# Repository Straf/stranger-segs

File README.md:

STRANGER SEGS
=============

An hardware platform to play with 7-segment displays.

This project was submitted to the montly challenge of the Element14 community (April 2022).
This repository contains all the artifacts developed for the challenge.

What you need
-------------

* The schematics and the PCB were produced with [KiCad 5.1.12](https://www.kicad.org).

* The firmware of the two applications was developed with [Microchip MPLAB X IDE 6.00](https://www.microchip.com/en-us/tools-resources/develop/mplab-x-ide) and the [Microchip AVR-GCC 5.4.0](https://www.microchip.com/en-us/tools-resources/develop/microchip-studio/gcc-compilers).

    - The first application is a **minimalist** racing game which may be played with a key and a display.

    - The second application is the firmware of a smart display module. Each module may be chained to others or composed in arbitrary display trees.

* The application to feed the display chain with data can be compiled with any **GCC** toolchain for a POSIX system. The build system is `make`. Built and tested on **macOS**, with [VSCode](https://code.visualstudio.com) as the IDE. It may work with Linux and [Cygwin](https://www.cygwin.com) for Windows.

### To build the firmware

1. First open the project with MPLAB X (some `makefile`s must be regenerated by the IDE).

2. Choose the exact part which you wish to use. The firmware should work with any **tinyavr 0** or **tinyavr 1** with enough RAM and flash to run the application. The game requires ~3KB of flash. The smart module less than 2KB. The use of RAM is negligible. The hardware module requires a **20-Pin VQFN** package.

3. Install the Device Family Pack of the part you wish to use.

4. Finally, build the application.

### To program the firmware into a module

To be programmed, the hardware module requires a [6-pin Tag-Connect cable](https://www.tag-connect.com/product-category/products/cables/6-pin-target) and a compatible programming tool, such as the **Atmel-ICE** or the **PicKit4**.

Since the **tinyavr** used have a **UPDI** interface, you may also use a simple USB-to-serial adapter with [pymcuprog](https://github.com/microchip-pic-avr-tools/pymcuprog).

### To build the driver application

A simple `make` should suffice.

Other resources
---------------

The project is described in two blog posts in the E14 community.

* The [first post](https://community.element14.com/challenges-projects/project14/7segmentdisplay/b/blog/posts/stranger-segs);

* The [second post](https://community.element14.com/challenges-projects/project14/7segmentdisplay/b/blog/posts/stranger-segs---season-two).

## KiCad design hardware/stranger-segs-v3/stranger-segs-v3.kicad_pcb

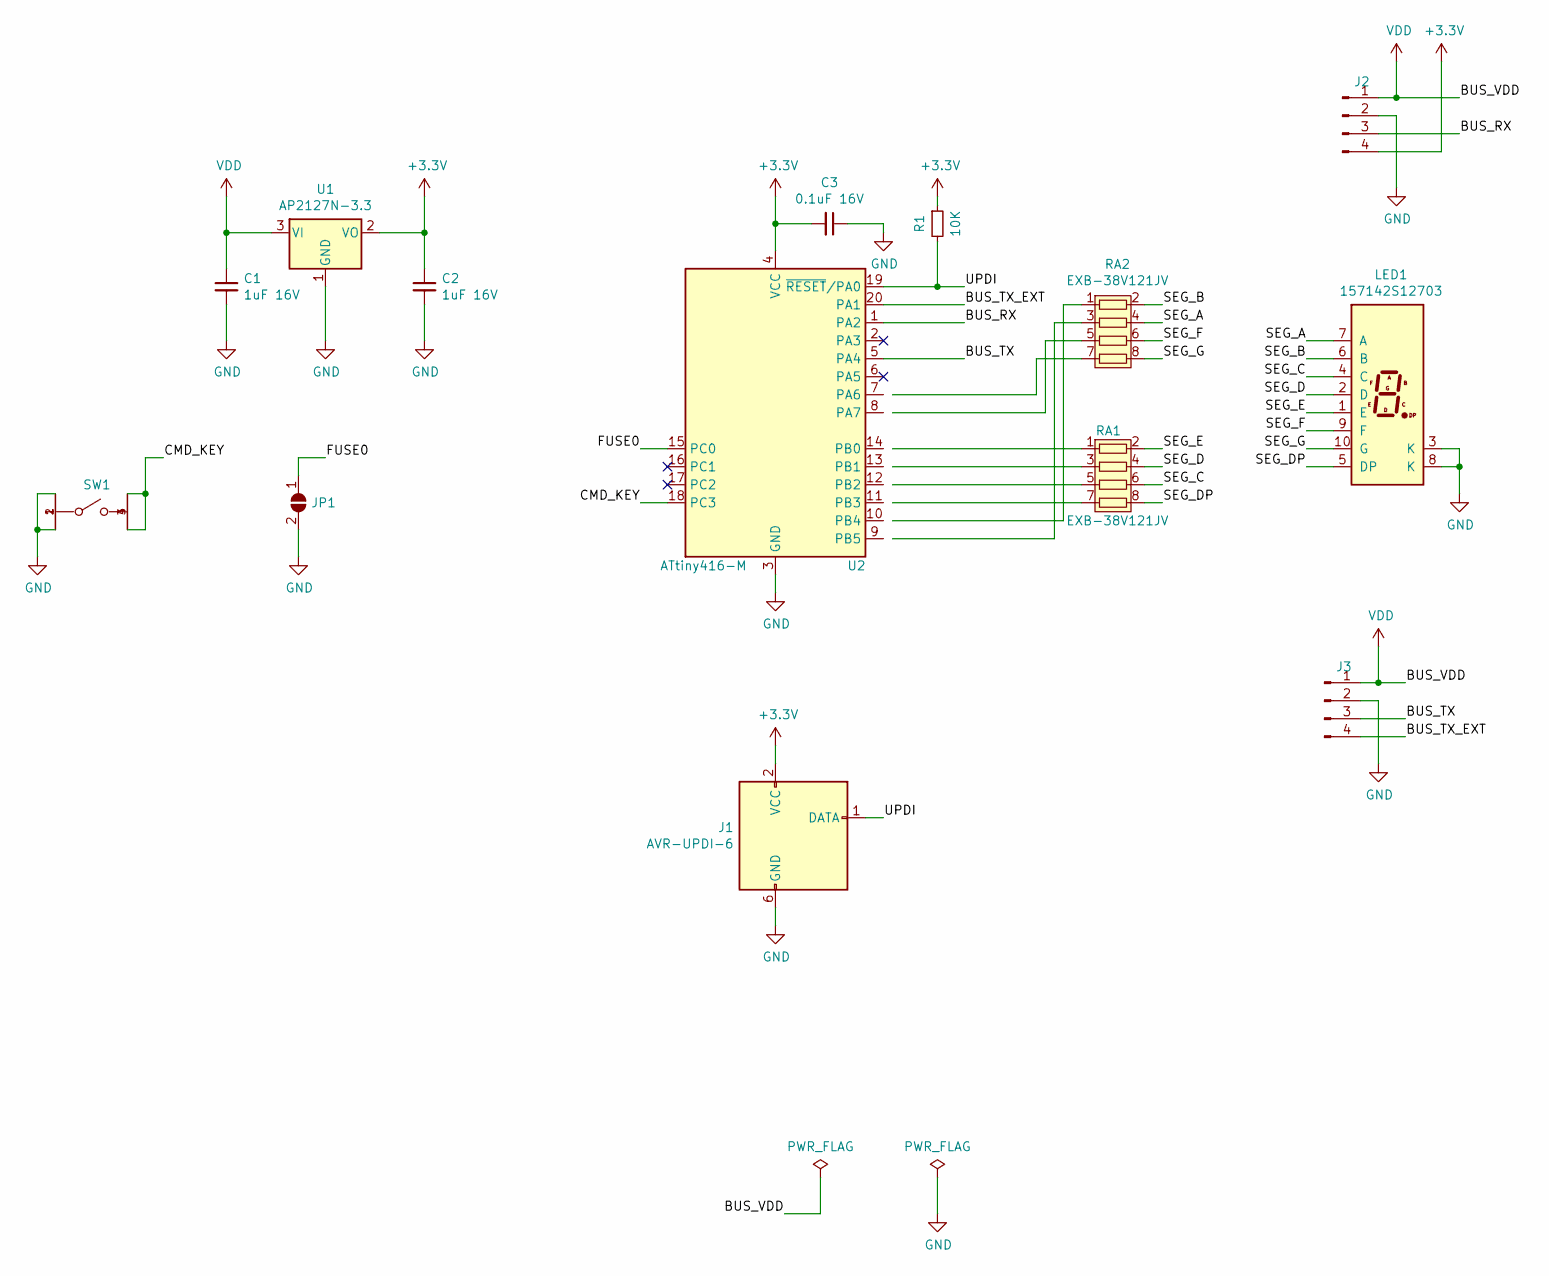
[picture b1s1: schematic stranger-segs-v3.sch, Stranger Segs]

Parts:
C1, C2: 1uF 16V; C_0603_1608Metric
C3: 0.1uF 16V; C_0603_1608Metric
J1: AVR-UPDI-6; Tag-Connect_TC2030-IDC-NL_2x03_P1.27mm_Vertical
J2, J3: Conn_01x04_Male; PinHeader_1x04_P2.54mm_Vertical
JP1: SolderJumper_2_Open; SolderJumper-2_P1.3mm_Open_TrianglePad1.0x1.5mm
LED1: 157142S12703; WL-T7DS_19x12x8
R1: 10K; R_0603_1608Metric
RA1, RA2: EXB-38V121JV; R_Array_EXB38V
SW1: PTS526SK15SMTR2LFS; SW_TH_Tactile_Omron_B3F-10xx; voltage rating DC 12V; mouser part number 611-PTS526SK15SMR2L; digikey description TACT 5.2 X 5.2, 1.5 MM H, 260GF,
U1: AP2127N-3.3; SOT-23
U2: ATtiny416-M; VQFN-20-1EP_3x3mm_P0.4mm_EP1.7x1.7mm

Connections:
+3V3: C2.1, C3.2, J1.2 (VCC), J2.4, R1.1, U1.2 (VO), U2.4 (VCC)
/BUS_RX: J2.3, U2.1 (PA2)
/BUS_TX: J3.3, U2.5 (PA4)
/BUS_TX_EXT: J3.4, U2.20 (PA1)
/CMD_KEY: SW1.3, SW1.4, U2.18 (PC3)
/FUSE0: JP1.1 (A), U2.15 (PC0)
/SEG_A: LED1.7 (A), RA2.4
/SEG_B: LED1.6 (B), RA2.2
/SEG_C: LED1.4 (C), RA1.6
/SEG_D: LED1.2 (D), RA1.4
/SEG_DP: LED1.5 (DP), RA1.8
/SEG_E: LED1.1 (E), RA1.2
/SEG_F: LED1.9 (F), RA2.6
/SEG_G: LED1.10 (G), RA2.8
/UPDI: J1.1 (DATA), R1.2, U2.19 (~RESET~/PA0)
GND: C1.2, C2.2, C3.1, J1.6 (GND), J2.2, J3.2, JP1.2 (B), LED1.3 (K), LED1.8 (K), SW1.1, SW1.2, U1.1 (GND), U2.3 (GND), U2.21 (GND)
VDD: C1.1, J2.1, J3.1, U1.3 (VI)

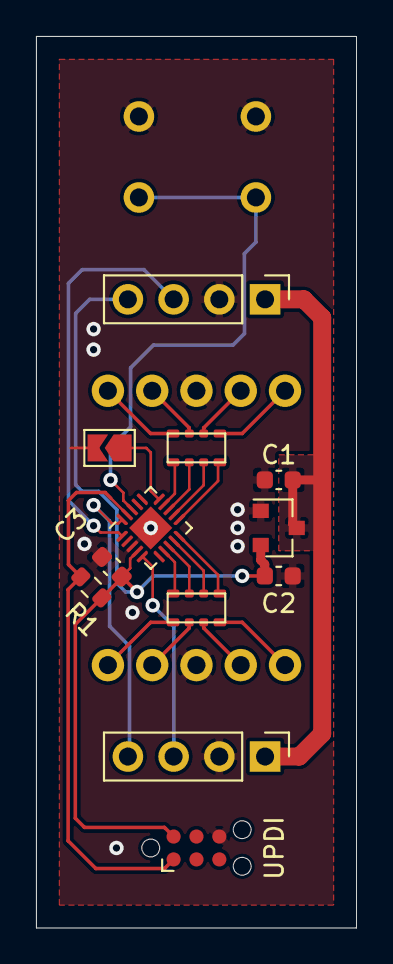
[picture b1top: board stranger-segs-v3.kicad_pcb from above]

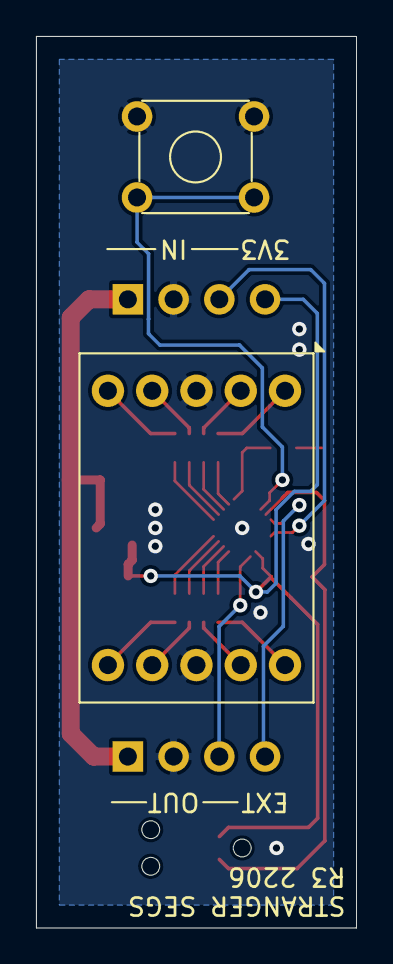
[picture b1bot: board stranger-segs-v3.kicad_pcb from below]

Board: 2 copper layers, 17.8 x 49.5 mm, 14 parts (2 on the bottom side), 17 nets.

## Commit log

2022-06-12 First commit.
2022-06-12 Added links to the relevant blog posts.
2022-07-03 Added racing game web emulation and compiled demo.
2022-07-03 Moved demo to another repo.
2022-07-03 Updated home URL.
